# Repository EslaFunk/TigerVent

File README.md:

# TigerVent #
## A Ventilator design inspired by Rice University's ApolloBMV with added Alarming and Pressure Sensing

Custom Enhancements from base ApolloBMV Design:
* Honeywell NSCDRRN001PDUNV Pressure Sensor integrated with driver (still available pressure sensor)
* Assist control mode that triggers the ventilator when negative pressure (a breath) is initiated
* Alarm/Buzzer and code to handle alarms based on pressure (WIP)
* Schematic and Board files for printed circuit board designed in EAGLE (confirmed tested and working)
* updated CAD file of chassis to fit PCB and CAD file of PCB
* alternate LCD driver implementation for more available 2004 LCD Screen
* Powershell script to automate updating library in seperate folder while also maintaining git capability

![alt text][renderedpcb]

WARNING: This product is not yet approved by any regulatory agency. Please consult with a medical professional prior to use, and use at your own risk.

Special thanks to the team at Rice University for the base design. Hopefully these enhancements can provide more functionality and safety to others looking to implement these ventilators.

[renderedpcb]: https://github.com/kebroad/TigerVent/blob/master/PrintedCircuitBoard/RenderedImage.png

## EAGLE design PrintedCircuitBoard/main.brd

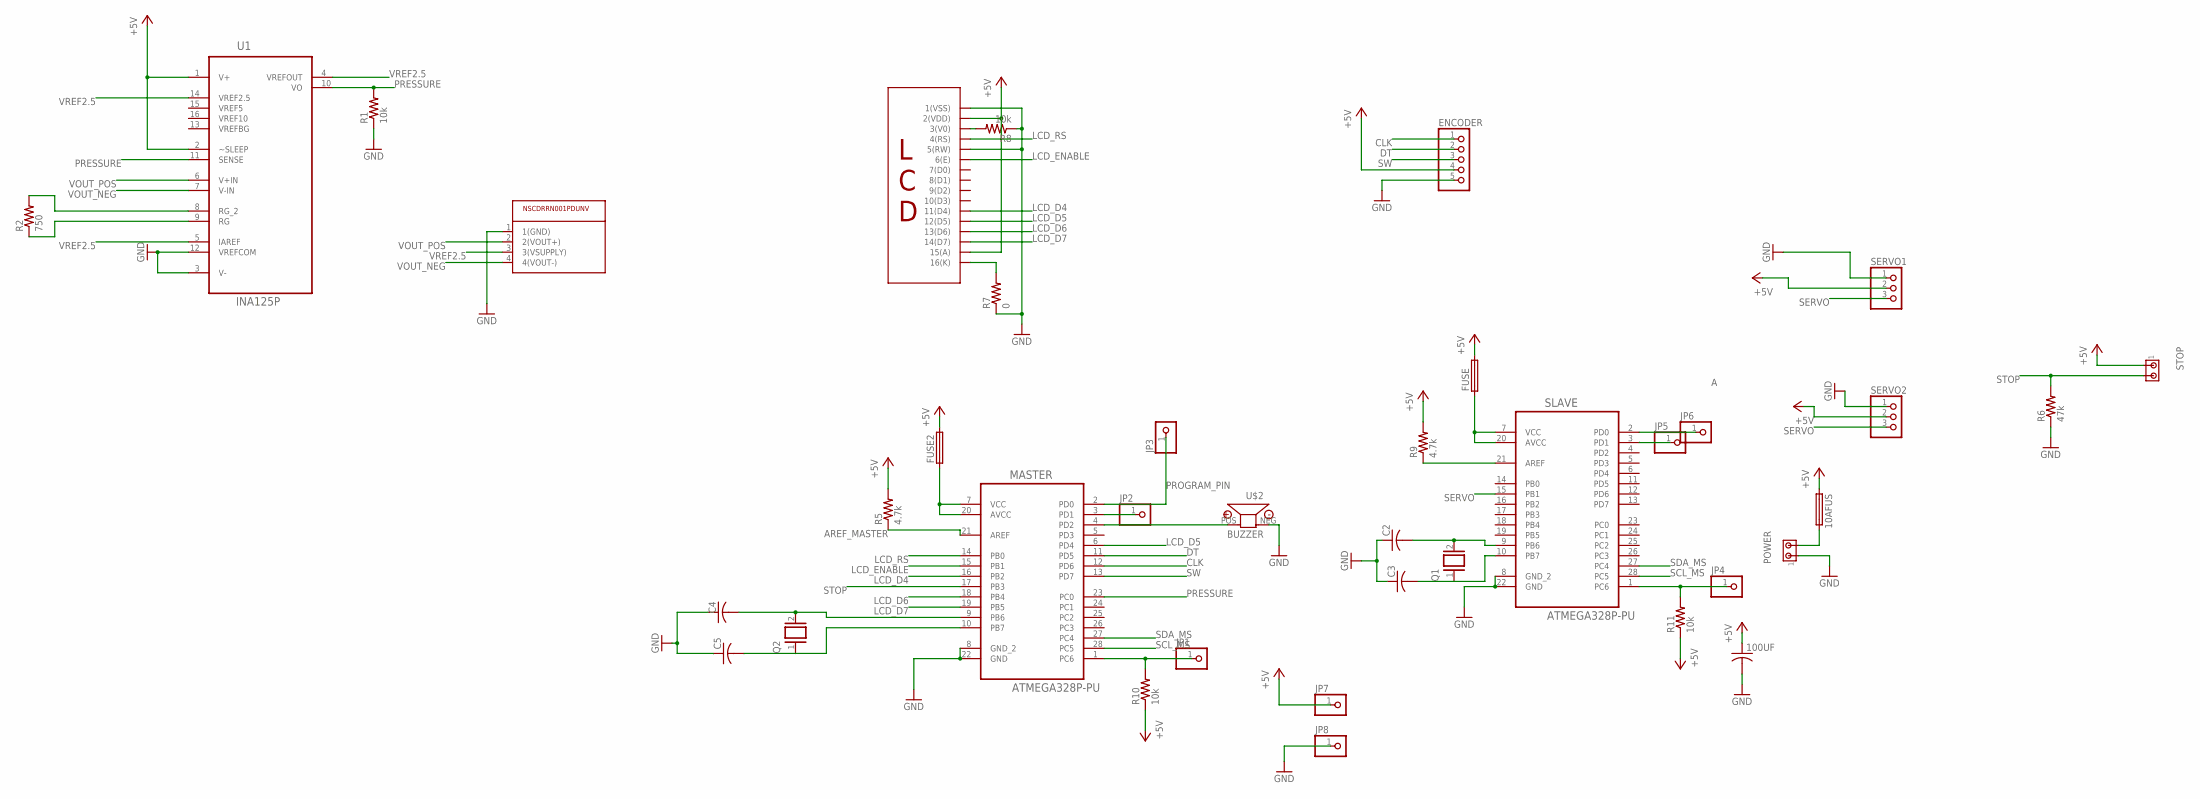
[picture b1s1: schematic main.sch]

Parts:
10AFUS: FUSE050-075X075; C050-075X075
100UF: 5MM_CAPACITOR050-075X075; C050-075X075
C2, C3, C4, C5: 5MM_CAPACITOR050-075X075; C050-075X075
ENCODER: PINHD-1X5; 1X05
FUSE, FUSE2: FUSE050-075X075; C050-075X075
JP1, JP2, JP3, JP4, JP5, JP6, JP7, JP8: PINHD-1X1; 1X01
MASTER: ATMEGA328P-PU; DIP254P762X457-28
POWER: MTA02-156; 1X2MTA
Q1, Q2: XTAL/S; QS
R1, R8, R10, R11: 10k; 0207/10
R2: 750; 0207/10
R5, R9: 4.7k; 0207/10
R6: 47k; 0207/10
R7: 0; 0207/10
SERVO1, SERVO2: PINHD-1X3/90; 1X03/90
SLAVE: ATMEGA328P-PU; DIP254P762X457-28
STOP: MTA02-156; 1X2MTA
U1: INA125P; DIP254P762X508-16
U$1: LCD; 1X16
U$2: BUZZER
U$3: PRESSURE_SENSOR; DIP8-WIDE

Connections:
+5V: 10AFUS.1, 100UF.1, ENCODER.4, FUSE.2, FUSE2.2, JP7.1, R5.2, R9.2, R10.1, R11.1, SERVO1.2, SERVO2.2, STOP.1, U1.1 (V+), U1.2 (~SLEEP), U$1.2 (2(VDD)), U$1.15 (15(A))
A: JP6.1, SLAVE.2 (PD0)
AREF_MASTER: MASTER.21 (AREF), R5.1
CLK: ENCODER.1, MASTER.12 (PD6)
DT: ENCODER.2, MASTER.11 (PD5)
GND: 100UF.2, C2.1, C3.1, C4.1, C5.1, ENCODER.5, JP8.1, MASTER.8 (GND_2), MASTER.22 (GND), POWER.1, R1.1, R6.1, R7.1, R8.1, SERVO1.1, SERVO2.1, SLAVE.8 (GND_2), SLAVE.22 (GND), U1.3 (V-), U1.12 (VREFCOM), U$1.1 (1(VSS)), U$1.5 (5(RW)), U$2.NEG, U$3.1 (1(GND))
LCD_D4: MASTER.16 (PB2), U$1.11 (11(D4))
LCD_D5: MASTER.6 (PD4), U$1.12 (12(D5))
LCD_D6: MASTER.18 (PB4), U$1.13 (13(D6))
LCD_D7: MASTER.19 (PB5), U$1.14 (14(D7))
LCD_ENABLE: MASTER.15 (PB1), U$1.6 (6(E))
LCD_RS: MASTER.14 (PB0), U$1.4 (4(RS))
unnamed: JP2.1, MASTER.3 (PD1)
unnamed: FUSE2.1, MASTER.7 (VCC), MASTER.20 (AVCC)
unnamed: FUSE.1, SLAVE.7 (VCC), SLAVE.20 (AVCC)
unnamed: 10AFUS.2, POWER.2
unnamed: R2.2, U1.8 (RG_2)
unnamed: C2.2, Q1.2, SLAVE.9 (PB6)
unnamed: C3.2, Q1.1, SLAVE.10 (PB7)
unnamed: JP1.1, MASTER.1 (PC6), R10.2
unnamed: JP4.1, R11.2, SLAVE.1 (PC6)
unnamed: C4.2, MASTER.9 (PB6), Q2.2
unnamed: JP5.1, SLAVE.3 (PD1)
unnamed: MASTER.4 (PD2), U$2.POS
unnamed: C5.2, MASTER.10 (PB7), Q2.1
unnamed: R7.2, U$1.16 (16(K))
unnamed: R8.2, U$1.3 (3(V0))
unnamed: R2.1, U1.9 (RG)
unnamed: R9.1, SLAVE.21 (AREF)
PRESSURE: MASTER.23 (PC0), R1.2, U1.10 (VO), U1.11 (SENSE)
PROGRAM_PIN: JP3.1, MASTER.2 (PD0)
SCL_MS: MASTER.28 (PC5), SLAVE.28 (PC5)
SDA_MS: MASTER.27 (PC4), SLAVE.27 (PC4)
SERVO: SERVO1.3, SERVO2.3, SLAVE.15 (PB1)
STOP: MASTER.17 (PB3), R6.2, STOP.2
SW: ENCODER.3, MASTER.13 (PD7)
VOUT_NEG: U1.7 (V-IN), U$3.4 (4(VOUT-))
VOUT_POS: U1.6 (V+IN), U$3.2 (2(VOUT+))
VREF2.5: U1.4 (VREFOUT), U1.5 (IAREF), U1.14 (VREF2.5), U$3.3 (3(VSUPPLY))
VREF5: U1.15 (VREF5)
VREF10: U1.16 (VREF10)
VREFBG: U1.13 (VREFBG)

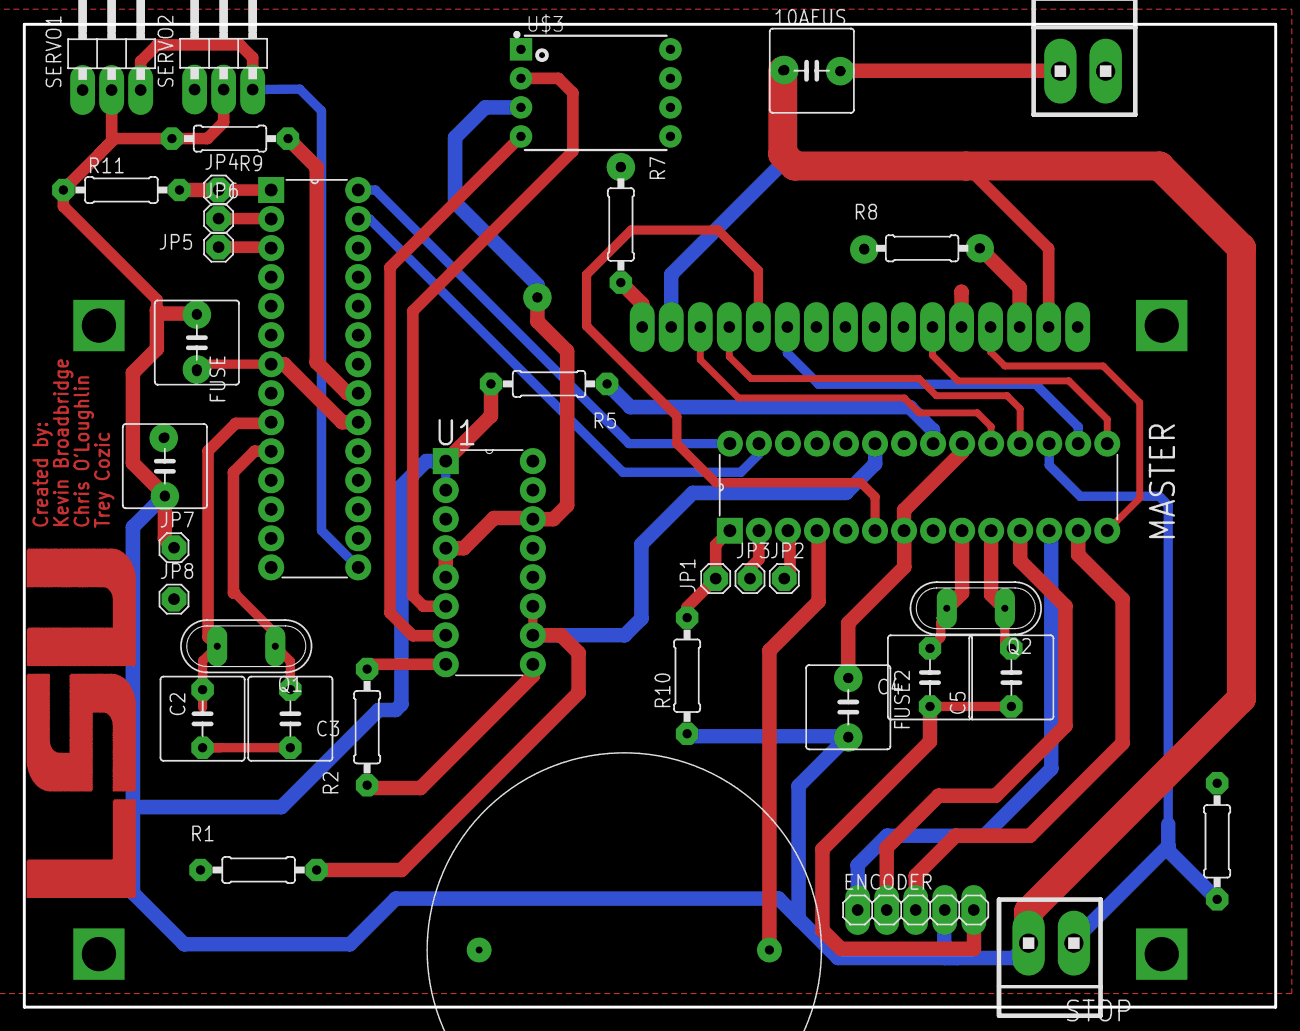
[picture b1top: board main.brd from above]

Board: 2 copper layers, 109.5 x 86.0 mm, 38 parts (1 on the bottom side), 39 nets.

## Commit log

2020-04-09 initial commit; added support for standard 2004 LCD
2020-04-10 Completed integration with LCD2004 driver
2020-04-15 Added to gitignore
2020-04-15 moved LCD driver to src folder
2020-04-17 added pressure sensor
2020-04-17 Changed pin for updated schematic
2020-04-17 fixed pin
2020-04-22 Changed LCD pins
2020-04-22 updated gitignore
2020-04-25 implemented buzzer and pressure sensor drivers
2020-04-26 Implemented alarm panel and high pressure alarm
2020-04-27 Integrated modes and mode switching
2020-04-27 implemented modes and mode switching
2020-04-29 implemented AC mode
2020-04-30 changed folder name
2020-04-30 changed name of library folder
2020-04-30 changed folder structure in Copy-ArduinoLibrary
2020-04-30 Added PCB files
2020-04-30 added rendered image of PCB
2020-04-30 added image
2020-04-30 fixed title
2020-04-30 added 3d files
2020-04-30 cropped rendered image
2020-05-01 added CAD files in readme
2020-05-01 updated readme.
2020-05-01 added warning to readme
2020-05-02 added programming in-board documentation
2020-05-02 updated tutorials
2020-05-02 updated tutorial
2020-05-02 updated in-socket programming
2020-05-02 updated images
2020-05-02 updated pressure sensor documentation
2020-05-02 updated documentation
2020-05-02 updated pressure sensor tutorial
